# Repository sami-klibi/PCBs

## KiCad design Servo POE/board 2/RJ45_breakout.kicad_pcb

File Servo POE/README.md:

Servo Distribution System (RJ45-Based)

A two-board system designed to simplify and organize the connection of up to 15 servos using standard Ethernet (RJ45) cables.

#### 📌 Board 1 – RJ45 Adapter for Adafruit 16-Channel Servo Driver

- Plugs into Adafruit PCA9685 driver
- **3x RJ45 ports**, each carrying:
  - 5 PWM lines
  - VCC
  - GND

#### 📌 Board 2 – Servo Breakout Board

- Takes 1 RJ45 cable as input
- Breaks out to **5x 3-pin servo connectors**
- Reduces cabling clutter and improves reliability

**🖼️ Images:**

**📄 Schematic:**
[View PDF](servoschematic.pdf)

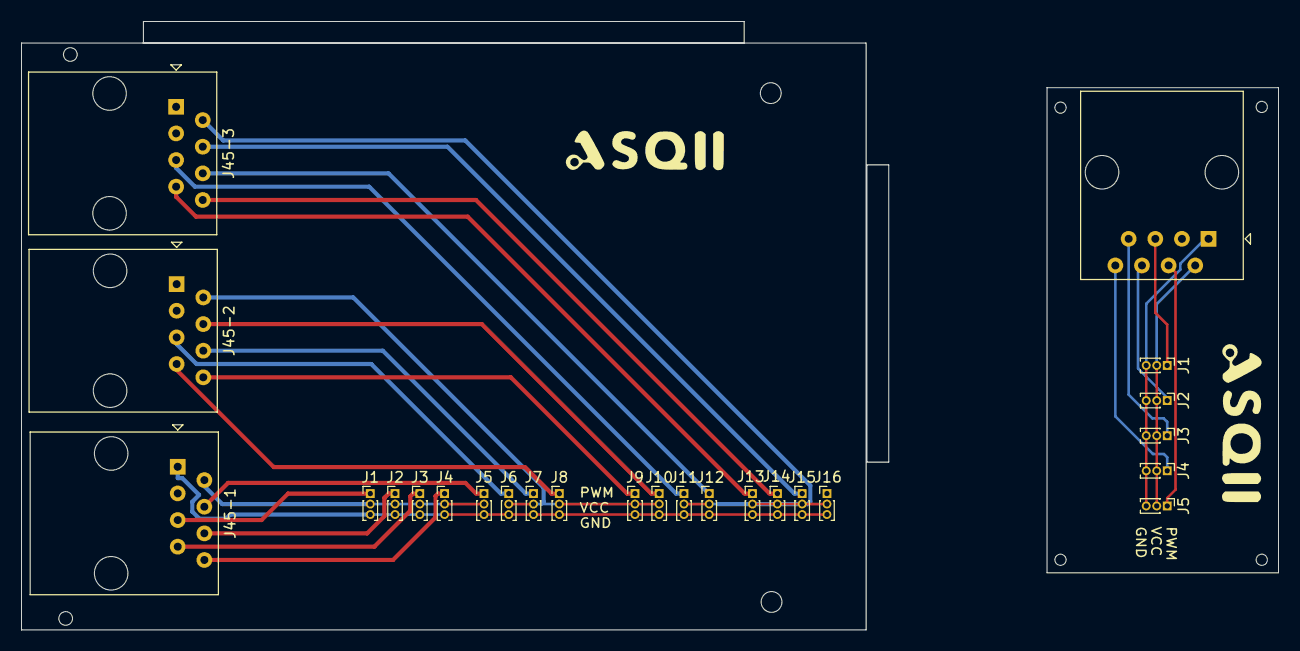
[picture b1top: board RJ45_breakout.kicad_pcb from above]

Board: 2 copper layers, 119.9 x 58.0 mm, 25 parts (0 on the bottom side), 19 nets.

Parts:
J1, J1#2, J2, J2#2, J3, J3#2, J4, J4#2, J5, J5#2, J6, J7, J8, J9, J10, J11, J12, J13, J14, J15, J16: Conn_01x03; PinHeader_1x03_P1.00mm_Vertical
J45-1, J45-1#2, J45-2, J45-3: RJ45; RJ45_Amphenol_54602-x08_Horizontal

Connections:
GND: J1.3 (GND), J1#2.3 (GND), J2.3 (GND), J2#2.3 (GND), J3.3 (GND), J3#2.3 (GND), J4.3 (GND), J4#2.3 (GND), J5.3 (GND), J5#2.3 (GND), J6.3 (GND), J7.3 (GND), J8.3 (GND), J9.3 (GND), J10.3 (GND), J11.3 (GND), J12.3 (GND), J13.3 (GND), J14.3 (GND), J15.3 (GND), J16.3 (GND), J45-1.1, J45-1#2.1
unnamed: J1.1 (PWM), J1#2.1 (PWM), J45-1.5, J45-1#2.5
unnamed: J1.2 (V+), J1#2.2 (V+), J2.2 (V+), J2#2.2 (V+), J3.2 (V+), J3#2.2 (V+), J4.2 (V+), J4#2.2 (V+), J5.2 (V+), J5#2.2 (V+), J45-1.2, J45-1#2.2
unnamed: J2.1 (PWM), J2#2.1 (PWM), J45-1.6, J45-1#2.6
unnamed: J3.1 (PWM), J3#2.1 (PWM), J45-1.7, J45-1#2.7
unnamed: J4.1 (PWM), J4#2.1 (PWM), J45-1.8, J45-1#2.8
unnamed: J5.1 (PWM), J5#2.1 (PWM), J45-1.4, J45-1#2.4
unnamed: J6.1 (PWM), J45-2.5
unnamed: J7.1 (PWM), J45-2.6
unnamed: J8.1 (PWM), J45-2.7
unnamed: J9.1 (PWM), J45-2.8
unnamed: J10.1 (PWM), J45-2.4
unnamed: J6.2 (V+), J7.2 (V+), J8.2 (V+), J9.2 (V+), J10.2 (V+), J45-2.2
unnamed: J11.1 (PWM), J45-3.5
unnamed: J11.2 (V+), J12.2 (V+), J13.2 (V+), J14.2 (V+), J15.2 (V+), J16.2 (V+), J45-3.2
unnamed: J12.1 (PWM), J45-3.6
unnamed: J13.1 (PWM), J45-3.7
unnamed: J14.1 (PWM), J45-3.8
unnamed: J15.1 (PWM), J45-3.4

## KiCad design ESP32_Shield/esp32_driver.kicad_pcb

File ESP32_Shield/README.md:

a custom shield designed for the ESP32, aimed at centralizing and simplifying the control of various system components. This board integrates several essential elements:

    🧠 A dedicated slot for the ESP32, ensuring a clean and stable integration of the microcontroller.

    🔄 A TMC2209 stepper motor driver, used for quiet and precise motor control.

    🔋 An LM2596 voltage regulator, selected with the help of the datasheet [5], to provide a stable power supply to the system.

    🔔 An integrated buzzer for simple audible alerts.

    💡 Status indicator LEDs, to visually monitor the state and operation of the system.

The shield also includes several connection ports:

    ⛓️ A port for a limit switch used for homing and position detection.

    🔗 An I2C communication port for connecting servo motor driver boards (e.g., PCA9685).

    🔌 A port for the stepper motor connection.

    🌬️ A port for a cooling fan, ensuring efficient thermal management.

This shield provides a centralized, compact, and efficient management solution for the system’s hardware, reducing wiring complexity and improving physical integration within the enclosure.

### Schematic Diagram
[📄 View PDF](espschematic.pdf)

 ### Routing

### 3D View

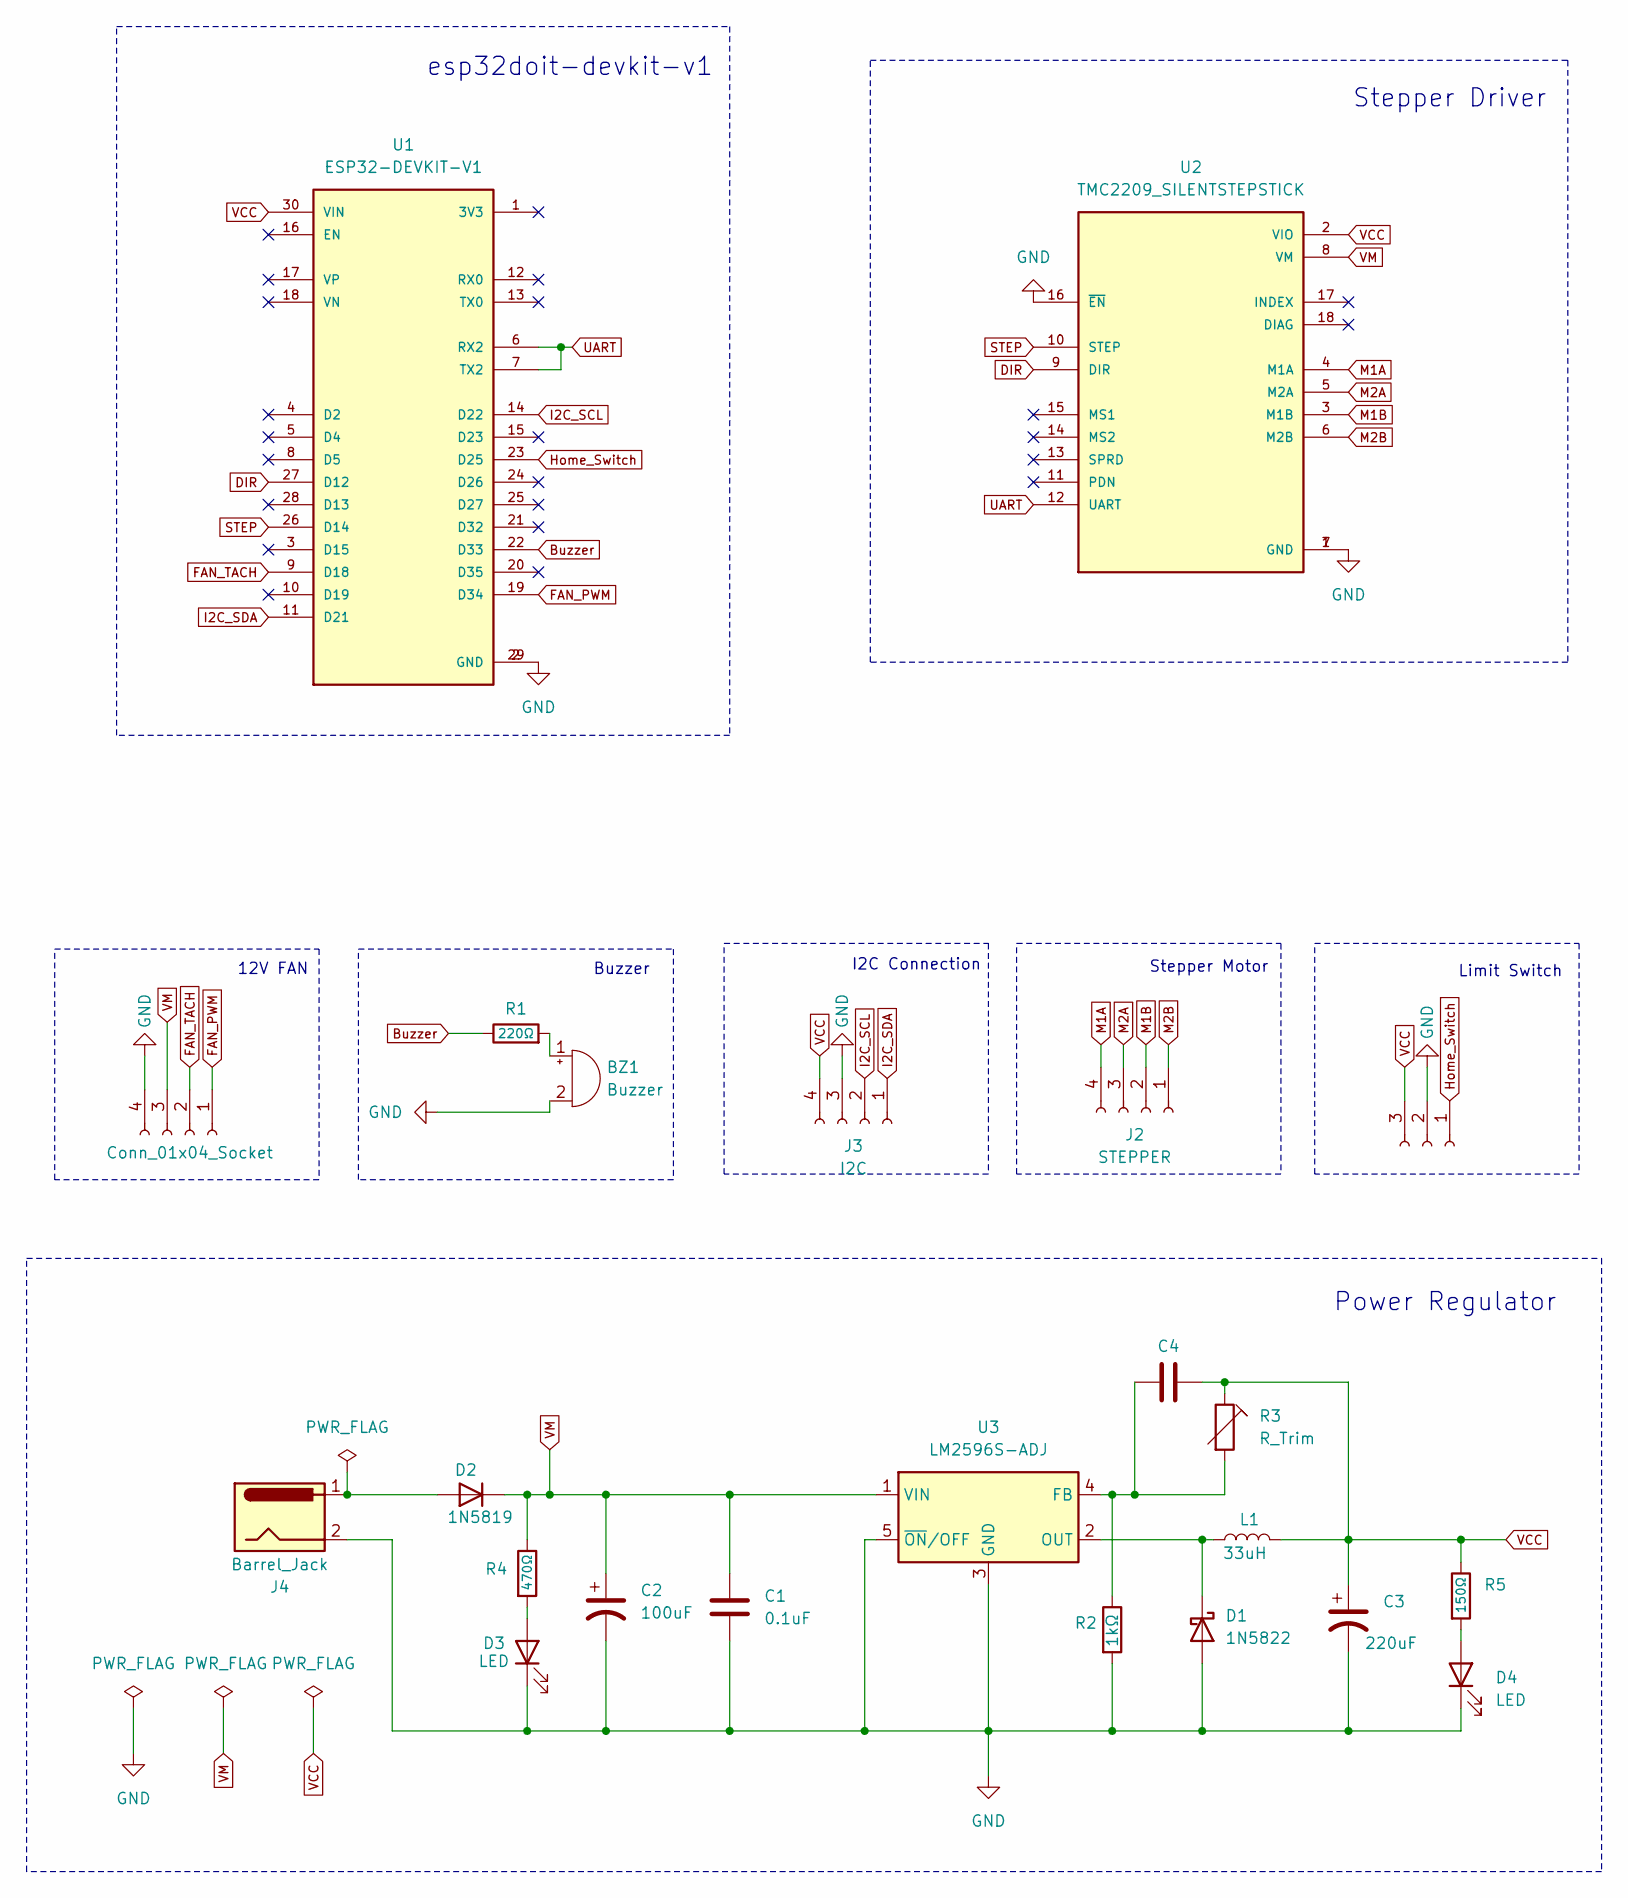
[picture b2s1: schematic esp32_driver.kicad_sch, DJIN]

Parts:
BZ1: Buzzer; Buzzer_12x9.5RM7.6
C1: 0.1uF; C_0603_1608Metric_Pad1.08x0.95mm_HandSolder
C2: 100uF; CP_Elec_8x10
C3: 220uF; CP_Elec_8x10
C4: C; C_0603_1608Metric_Pad1.08x0.95mm_HandSolder
D1: 1N5822; D_1206_3216Metric
D2: 1N5819; D_SOD-123
D3, D4: LED; LED_D3.0mm
Home_Switch1: Home_Switch; JST_XH_S3B-XH-A-1_1x03_P2.50mm_Horizontal
J2: STEPPER; JST_XH_S4B-XH-A_1x04_P2.50mm_Horizontal
J3: I2C; JST_XH_S4B-XH-A_1x04_P2.50mm_Horizontal
J4: Barrel_Jack; BarrelJack_Horizontal
J5: Conn_01x04_Socket; JST_XH_B4B-XH-A_1x04_P2.50mm_Vertical
L1: 33uH; L_12x12mm_H8mm
R1: 220Ω; R_0603_1608Metric
R2: 1kΩ; R_0603_1608Metric
R3: R_Trim; Potentiometer_Bourns_3296W_Vertical
R4: 470Ω; R_0603_1608Metric
R5: 150Ω; R_0603_1608Metric
U1: ESP32-DEVKIT-V1; MODULE_ESP32_DEVKIT_V1; PARTREV N/A
U2: TMC2209_SILENTSTEPSTICK; MODULE_TMC2209_SILENTSTEPSTICK; PARTREV 1.20
U3: LM2596S-ADJ; TO-263-5_TabPin3

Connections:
Buzzer: R1.1, U1.22 (D33)
DIR: U1.27 (D12), U2.9 (DIR)
FAN_PWM: J5.1, U1.19 (D34)
FAN_TACH: J5.2, U1.9 (D18)
GND: BZ1.2 (-), C1.2, C2.2, C3.2, D1.2 (A), D3.1 (K), D4.1 (K), Home_Switch1.2, J3.3, J4.2, J5.4, R2.2, U1.2 (GND), U1.29 (GND), U2.1 (GND), U2.7 (GND), U2.16 (~EN), U3.3 (GND), U3.5 (~ON/OFF); also elsewhere on the board
Home_Switch: Home_Switch1.1, U1.23 (D25); also elsewhere on the board
I2C_SCL: J3.2, U1.14 (D22)
I2C_SDA: J3.1, U1.11 (D21)
M1A: J2.4, U2.4 (M1A)
M1B: J2.2, U2.3 (M1B)
M2A: J2.3, U2.5 (M2A)
M2B: J2.1, U2.6 (M2B)
unnamed: BZ1.1 (+), R1.2
unnamed: D1.1 (K), L1.1, U3.2 (OUT)
unnamed: D2.2 (A), J4.1
unnamed: D3.2 (A), R4.2
unnamed: D4.2 (A), R5.2
unnamed: C4.1, R2.1, R3.2, U3.4 (FB)
STEP: U1.26 (D14), U2.10 (STEP)
UART: U1.6 (RX2), U1.7 (TX2), U2.12 (UART)
VCC: C3.1, C4.2, Home_Switch1.3, J3.4, L1.2, R3.1, R5.1, U1.30 (VIN), U2.2 (VIO); also elsewhere on the board
VM: C1.1, C2.1, D2.1 (K), J5.3, R4.1, U2.8 (VM), U3.1 (VIN)

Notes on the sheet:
Limit Switch
Buzzer
12V FAN
Power Regulator
Stepper Motor
Stepper Driver
esp32doit-devkit-v1
I2C Connection

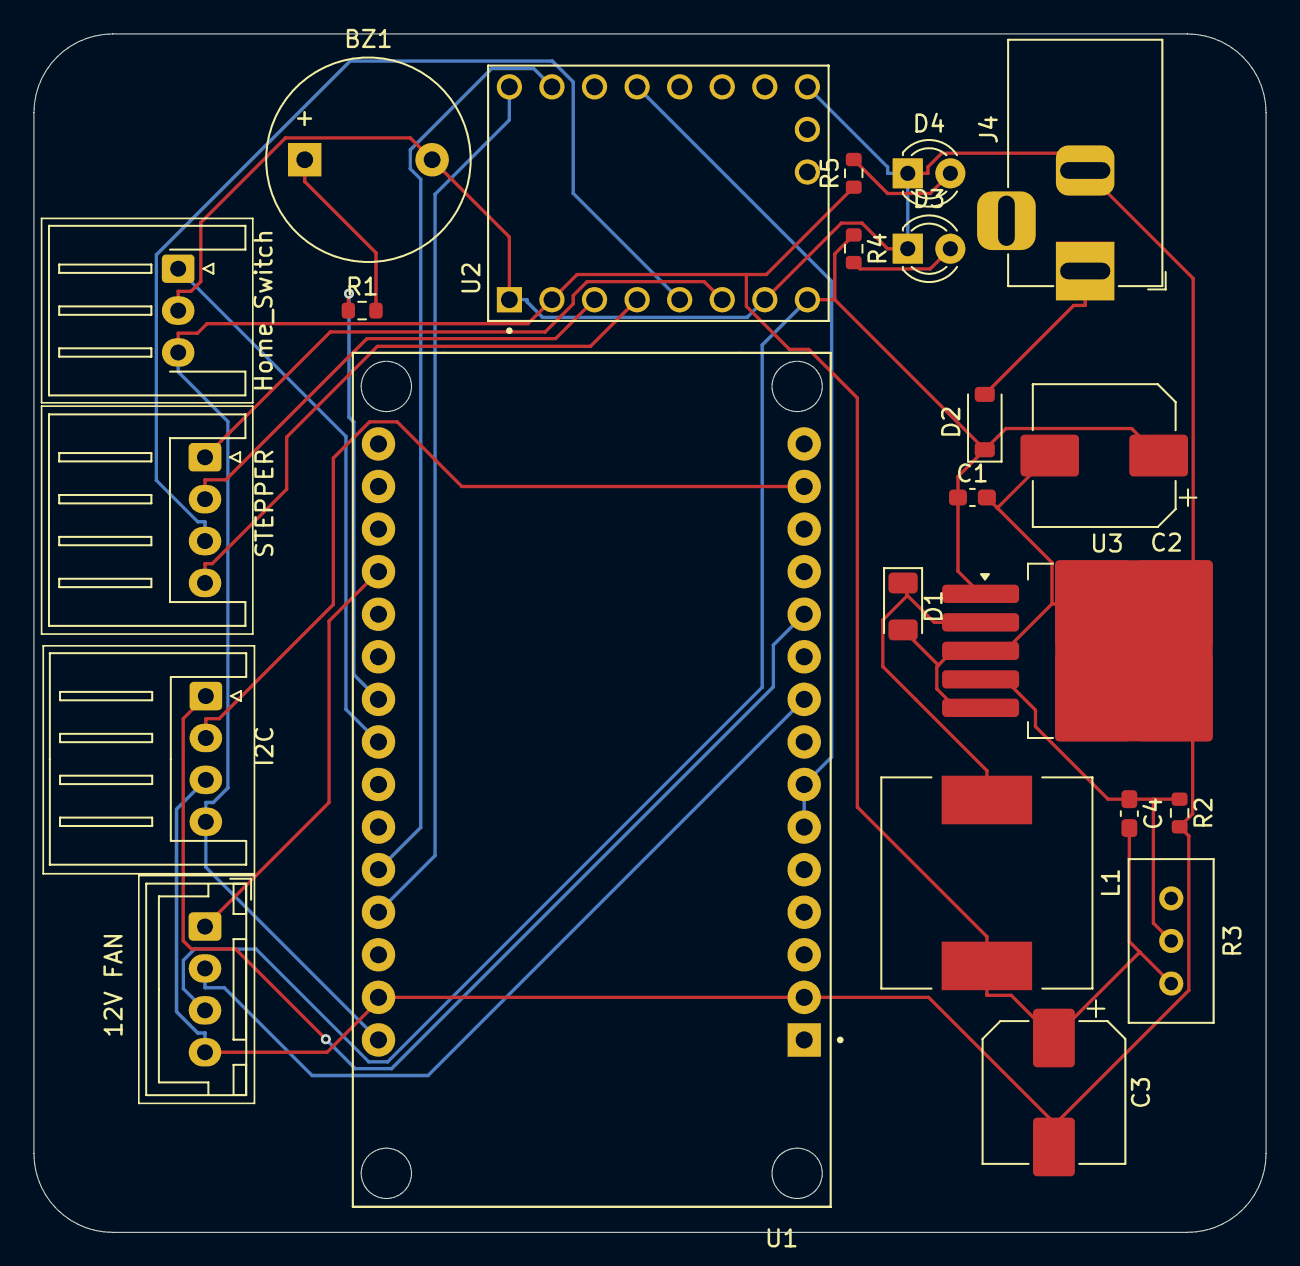
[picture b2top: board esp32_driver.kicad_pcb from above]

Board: 2 copper layers, 73.5 x 71.5 mm, 23 parts (0 on the bottom side), 22 nets.

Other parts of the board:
Home_Switch: Home_Switch; JST_XH_S3B-XH-A-1_1x03_P2.50mm_Horizontal

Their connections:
GND: Home_Switch.2; also elsewhere on the board
Home_Switch: Home_Switch.1; also elsewhere on the board
VCC: Home_Switch.3; also elsewhere on the board

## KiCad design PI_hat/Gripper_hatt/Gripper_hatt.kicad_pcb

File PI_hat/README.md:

# 🧠 Custom Raspberry Pi Hat for Stepper and Servo Control

This project is a custom PCB designed to **replace the Arduino + CNC Shield v4 setup** with a **more compact and integrated solution**, tailored to the specific needs of our automated machine.

## 🚀 Why This PCB?

This board was developed in collaboration with [Company Name] to optimize space, improve performance, and simplify wiring when interfacing with the Raspberry Pi 4.

### 🧩 Key Features

- 🔄 **2x TMC2209 Stepper Drivers**  
  Ultra-silent and precise stepper control with UART configuration.

- ⚙️ **2x Servo Motor Connectors**  
  Designed to control the gripper's movement directly.

- 🧱 **3x Endstop Inputs**  
  Ensures reliable homing and positional accuracy.

- 🌬️ **Fan Connector (5V)**  
  Keeps your electronics cool during operation.

- 🔌 **GPIO-Optimized for Raspberry Pi 4**  
  Carefully routed for clean integration and minimal cabling.

## 📐 PCB Overview

## 🖼️ Top View

## 🗺️ Schematic Diagram
📄 [View PDF](Gripper_hatt/schematic.pdf)

## 🧱 3D Render

## 🔧 Installed Example

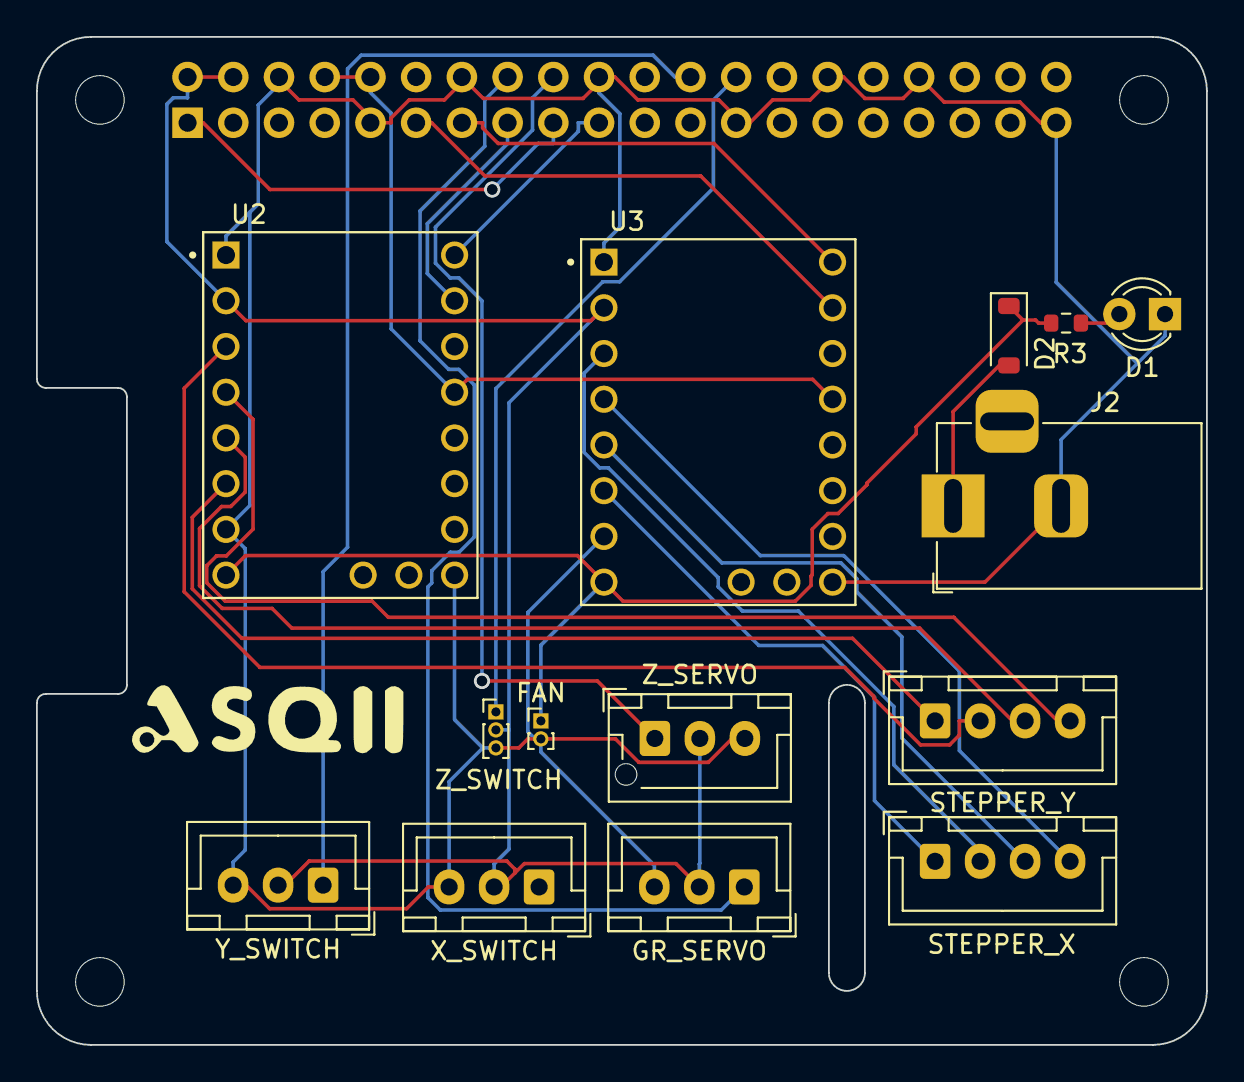
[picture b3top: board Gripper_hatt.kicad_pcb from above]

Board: 2 copper layers, 65.0 x 56.0 mm, 19 parts (1 on the bottom side), 24 nets.

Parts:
D1: LED; LED_D3.0mm
D2: 1N5819; D_SOD-123
FAN: FAN; PinHeader_1x02_P1.00mm_Vertical
GR_SERVO: GR_SERVO; JST_XH_B3B-XH-A_1x03_P2.50mm_Vertical
J1: GPIO; PinSocket_2x20_P2.54mm_Vertical
J2: Barrel_Jack; BarrelJack_Horizontal
MH1, MH2, MH3, MH4: MountingHole_2.7mm_M2.5
R3: 470Ω; R_0603_1608Metric
STEPPER_X: STEPPER_X; JST_XH_B4B-XH-A_1x04_P2.50mm_Vertical
STEPPER_Y: STEPPER_Y; JST_XH_B4B-XH-A_1x04_P2.50mm_Vertical
U2, U3: TMC2209_SILENTSTEPSTICK; MODULE_TMC2209_SILENTSTEPSTICK
X_SWITCH: X_SWITCH; JST_XH_B3B-XH-A_1x03_P2.50mm_Vertical
Y_SWITCH: Y_SWITCH; JST_XH_B3B-XH-A_1x03_P2.50mm_Vertical
Z_SERVO: Z_SERVO; JST_XH_B3B-XH-AM_1x03_P2.50mm_Vertical
Z_SWITCH: Z_SWITCH; PinHeader_1x03_P1.00mm_Vertical

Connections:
+3V3: J1.1, J1.17
+5V: GR_SERVO.2, J1.2, J1.4, U2.2 (VIO), U3.2 (VIO), X_SWITCH.2, Y_SWITCH.2, Z_SERVO.2, Z_SWITCH.2
DIR_1: J1.13, U3.9 (DIR)
DIR_2: J1.19, U2.9 (DIR)
GND: D1.1 (K), FAN.2, GR_SERVO.3, J1.6, J1.9, J1.14, J1.20, J1.25, J1.30, J1.34, J1.39, J2.2, U2.1 (GND), U2.7 (GND), U2.16 (~EN), U3.1 (GND), U3.7 (GND), U3.16 (~EN), X_SWITCH.3, Y_SWITCH.3, Z_SERVO.3, Z_SWITCH.3
GR_SERVO: GR_SERVO.1, J1.16
M1A1: STEPPER_X.4, U3.4 (M1A)
M1A2: STEPPER_Y.4, U2.4 (M1A)
M1B1: STEPPER_X.2, U3.3 (M1B)
M1B2: STEPPER_Y.2, U2.3 (M1B)
M2A1: STEPPER_X.3, U3.5 (M2A)
M2A2: STEPPER_Y.3, U2.5 (M2A)
M2B1: STEPPER_X.1, U3.6 (M2B)
M2B2: STEPPER_Y.1, U2.6 (M2B)
unnamed: D1.2 (A), R3.1
unnamed: D2.2 (A), J2.1
STEP_1: J1.11, U3.10 (STEP)
STEP_2: J1.15, U2.10 (STEP)
UART: J1.8, J1.10, U2.12 (UART), U3.12 (UART)
VM: D2.1 (K), FAN.1, R3.2, U2.8 (VM), U3.8 (VM)
X_SWITCH: J1.22, X_SWITCH.1
Y_SWITCH: J1.24, Y_SWITCH.1
Z_SERVO: J1.18, Z_SERVO.1
Z_SWITCH: J1.26, Z_SWITCH.1

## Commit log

2025-06-06 Create Images
2025-06-08 Create ESP32-Driver
2025-06-08 Create routing
2025-06-08 Rename Screenshot 2025-06-08 085425.png to 3d view
2025-06-08 Rename Screenshot 2025-06-08 085416.png to routing
2025-06-08 Rename 3d view to 3d view.png
2025-06-08 Rename routing to routing.png
2025-06-08 Rename 3d view.png to 3d_view.png
2025-06-08 Create img
2025-06-08 Rename Screenshot 2025-06-08 091829.png to board1.png
